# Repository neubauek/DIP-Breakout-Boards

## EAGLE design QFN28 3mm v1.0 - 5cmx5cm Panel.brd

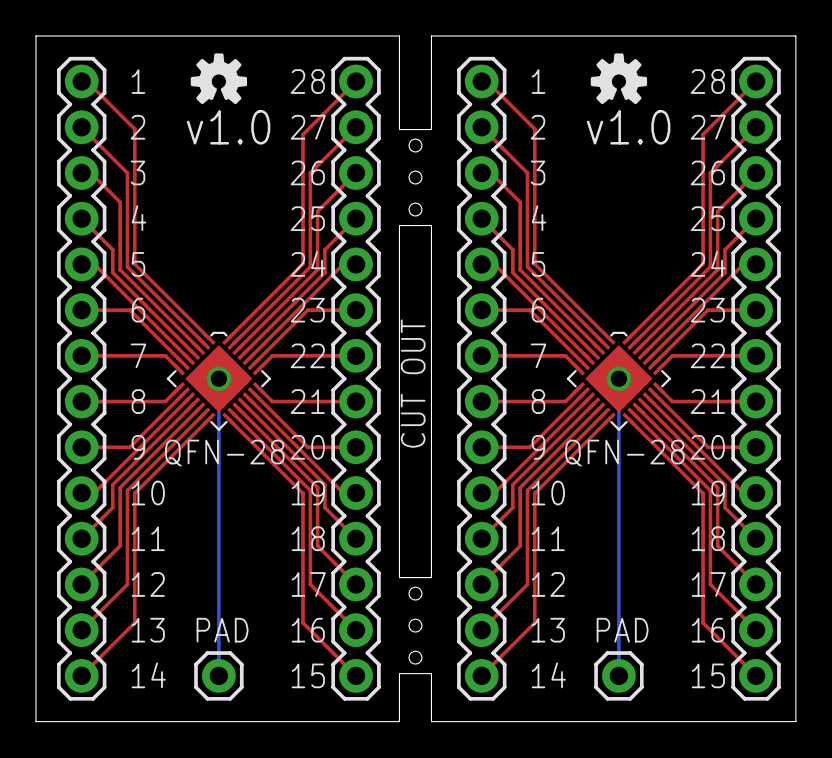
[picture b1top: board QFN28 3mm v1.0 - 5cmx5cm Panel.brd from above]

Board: 2 copper layers, 42.2 x 38.1 mm, 11 parts (0 on the bottom side), 58 nets.

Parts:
FRAME1: FRAME-LETTER; CREATIVE_COMMONS
JP1, JP2, JP3, JP4: M14; 1X14
PAD, PAD1: M01PTH; 1X01
U$1, U$3: QFN-28
U$2, U$4: OSHW-LOGO-S

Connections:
GND: PAD.1, U$1.29
GND1: PAD1.1, U$3.29
unnamed: JP1.14, U$1.1
unnamed: JP1.13, U$1.2
unnamed: JP1.12, U$1.3
unnamed: JP1.11, U$1.4
unnamed: JP1.10, U$1.5
unnamed: JP1.9, U$1.6
unnamed: JP1.8, U$1.7
unnamed: JP1.7, U$1.8
unnamed: JP1.6, U$1.9
unnamed: JP1.5, U$1.10
unnamed: JP1.4, U$1.11
unnamed: JP1.3, U$1.12
unnamed: JP1.2, U$1.13
unnamed: JP1.1, U$1.14
unnamed: JP2.1, U$1.15
unnamed: JP2.2, U$1.16
unnamed: JP2.3, U$1.17
unnamed: JP2.4, U$1.18
unnamed: JP2.5, U$1.19
unnamed: JP2.6, U$1.20
unnamed: JP2.7, U$1.21
unnamed: JP2.8, U$1.22
unnamed: JP2.9, U$1.23
unnamed: JP2.10, U$1.24
unnamed: JP2.11, U$1.25
unnamed: JP2.12, U$1.26
unnamed: JP2.13, U$1.27
unnamed: JP2.14, U$1.28
unnamed: JP3.14, U$3.1
unnamed: JP3.13, U$3.2
unnamed: JP3.12, U$3.3
unnamed: JP3.11, U$3.4
unnamed: JP3.10, U$3.5
unnamed: JP3.9, U$3.6
unnamed: JP3.8, U$3.7
unnamed: JP3.7, U$3.8
unnamed: JP3.6, U$3.9
unnamed: JP3.5, U$3.10
unnamed: JP3.4, U$3.11
unnamed: JP3.3, U$3.12
unnamed: JP3.2, U$3.13
unnamed: JP3.1, U$3.14
unnamed: JP4.1, U$3.15
unnamed: JP4.2, U$3.16
unnamed: JP4.3, U$3.17
unnamed: JP4.4, U$3.18
unnamed: JP4.5, U$3.19
unnamed: JP4.6, U$3.20
unnamed: JP4.7, U$3.21
unnamed: JP4.8, U$3.22
unnamed: JP4.9, U$3.23
unnamed: JP4.10, U$3.24
unnamed: JP4.11, U$3.25
unnamed: JP4.12, U$3.26
unnamed: JP4.13, U$3.27
unnamed: JP4.14, U$3.28

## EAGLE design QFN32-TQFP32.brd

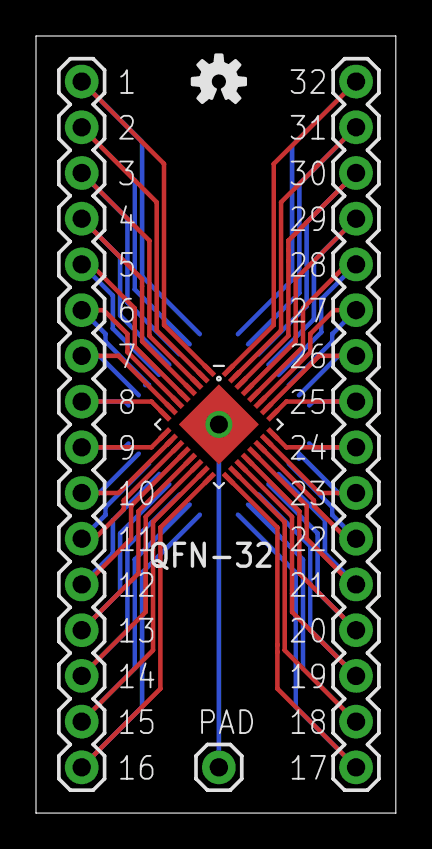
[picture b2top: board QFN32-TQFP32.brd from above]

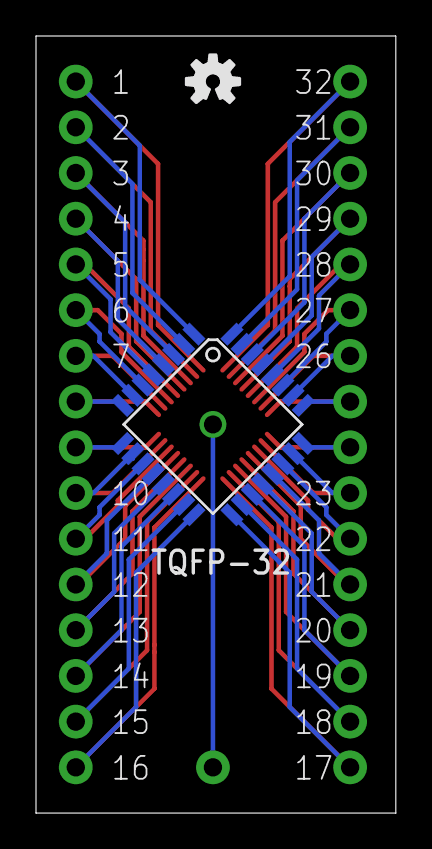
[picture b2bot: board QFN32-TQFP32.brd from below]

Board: 2 copper layers, 20.0 x 43.2 mm, 8 parts (2 on the bottom side), 33 nets.

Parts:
FRAME1: FRAME-LETTER; CREATIVE_COMMONS
JP1, JP2: M16PTH; 1X16
PAD: M01PTH; 1X01
QFN-32: QFN-32
TQFP-32: TQFP-3208MM; TQFP32-08
U$1, U$2: OSHW-LOGO-S

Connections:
GND: PAD.1, QFN-32.EP
unnamed: JP2.9, QFN-32.25, TQFP-32.8
unnamed: JP1.16, QFN-32.1, TQFP-32.32
unnamed: JP1.15, QFN-32.2, TQFP-32.31
unnamed: JP1.14, QFN-32.3, TQFP-32.30
unnamed: JP1.13, QFN-32.4, TQFP-32.29
unnamed: JP1.11, QFN-32.6, TQFP-32.27
unnamed: JP1.10, QFN-32.7, TQFP-32.26
unnamed: JP1.9, QFN-32.8, TQFP-32.25
unnamed: JP1.8, QFN-32.9, TQFP-32.24
unnamed: JP1.7, QFN-32.10, TQFP-32.23
unnamed: JP1.6, QFN-32.11, TQFP-32.22
unnamed: JP1.5, QFN-32.12, TQFP-32.21
unnamed: JP1.4, QFN-32.13, TQFP-32.20
unnamed: JP1.3, QFN-32.14, TQFP-32.19
unnamed: JP1.2, QFN-32.15, TQFP-32.18
unnamed: JP1.1, QFN-32.16, TQFP-32.17
unnamed: JP2.14, QFN-32.30, TQFP-32.3
unnamed: JP2.13, QFN-32.29, TQFP-32.4
unnamed: JP2.12, QFN-32.28, TQFP-32.5
unnamed: JP2.11, QFN-32.27, TQFP-32.6
unnamed: JP2.10, QFN-32.26, TQFP-32.7
unnamed: JP2.2, QFN-32.18, TQFP-32.15
unnamed: JP2.8, QFN-32.24, TQFP-32.9
unnamed: JP2.7, QFN-32.23, TQFP-32.10
unnamed: JP2.5, QFN-32.21, TQFP-32.12
unnamed: JP2.4, QFN-32.20, TQFP-32.13
unnamed: JP2.3, QFN-32.19, TQFP-32.14
unnamed: JP2.15, QFN-32.31, TQFP-32.2
unnamed: JP2.16, QFN-32.32, TQFP-32.1
unnamed: JP2.1, QFN-32.17, TQFP-32.16
unnamed: JP1.12, QFN-32.5, TQFP-32.28
unnamed: JP2.6, QFN-32.22, TQFP-32.11

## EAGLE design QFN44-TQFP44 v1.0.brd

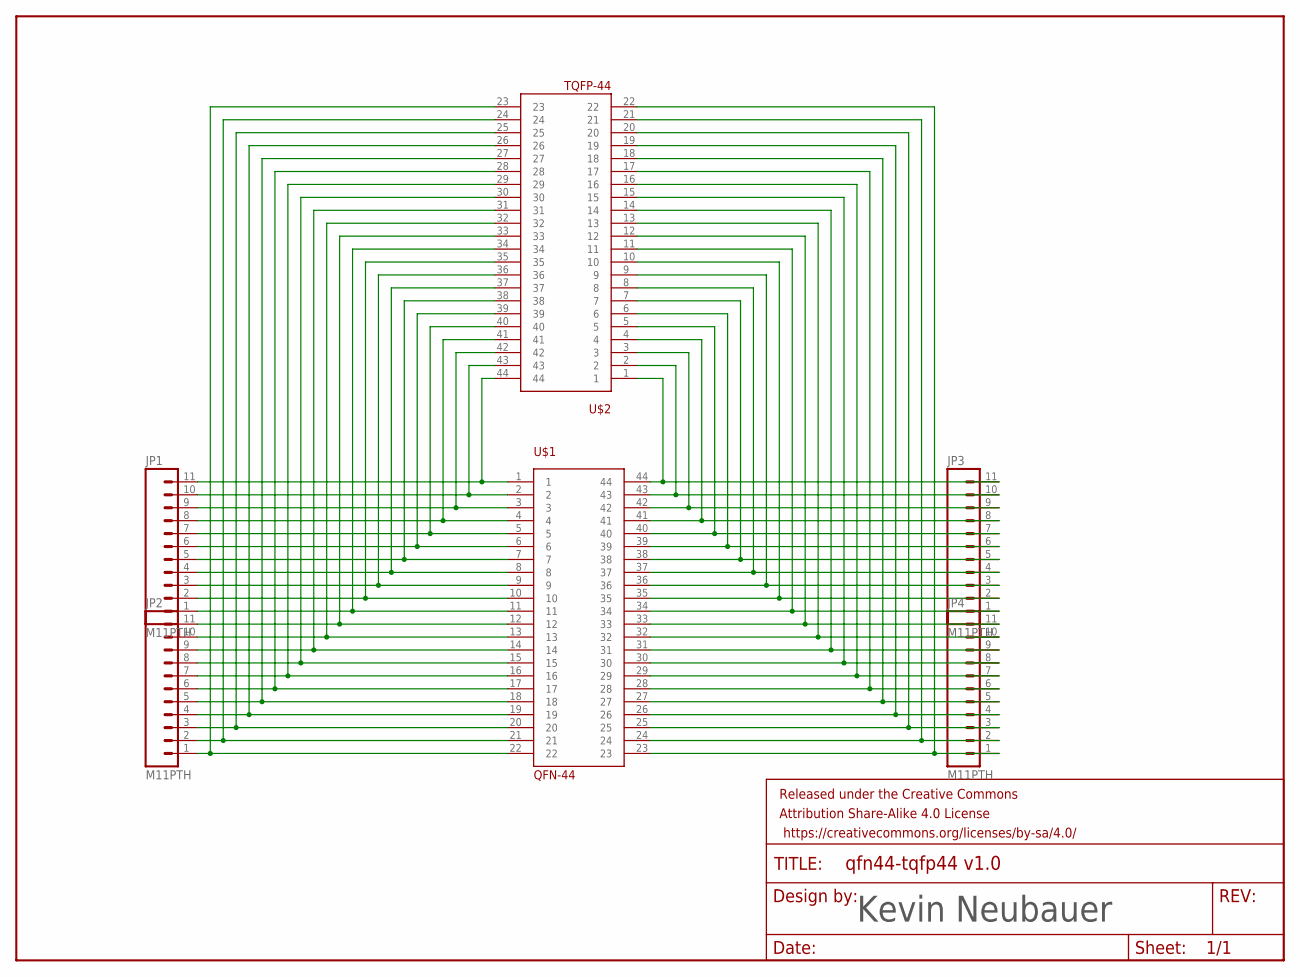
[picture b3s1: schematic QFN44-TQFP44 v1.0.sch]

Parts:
FRAME1: FRAME-LETTER; CREATIVE_COMMONS
JP1, JP2, JP3, JP4: M11PTH; 1X11
U$1: QFN-44
U$2: TQFP-44; TQFP44

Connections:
unnamed: JP1.11, U$1.1, U$2.44
unnamed: JP1.10, U$1.2, U$2.43
unnamed: JP1.9, U$1.3, U$2.42
unnamed: JP1.8, U$1.4, U$2.41
unnamed: JP1.7, U$1.5, U$2.40
unnamed: JP1.6, U$1.6, U$2.39
unnamed: JP1.5, U$1.7, U$2.38
unnamed: JP1.4, U$1.8, U$2.37
unnamed: JP1.3, U$1.9, U$2.36
unnamed: JP1.2, U$1.10, U$2.35
unnamed: JP1.1, U$1.11, U$2.34
unnamed: JP2.11, U$1.12, U$2.33
unnamed: JP2.10, U$1.13, U$2.32
unnamed: JP2.9, U$1.14, U$2.31
unnamed: JP2.8, U$1.15, U$2.30
unnamed: JP2.7, U$1.16, U$2.29
unnamed: JP2.6, U$1.17, U$2.28
unnamed: JP2.5, U$1.18, U$2.27
unnamed: JP2.4, U$1.19, U$2.26
unnamed: JP2.3, U$1.20, U$2.25
unnamed: JP2.2, U$1.21, U$2.24
unnamed: JP2.1, U$1.22, U$2.23
unnamed: JP3.11, U$1.44, U$2.1
unnamed: JP3.10, U$1.43, U$2.2
unnamed: JP3.7, U$1.40, U$2.5
unnamed: JP3.6, U$1.39, U$2.6
unnamed: JP3.5, U$1.38, U$2.7
unnamed: JP3.4, U$1.37, U$2.8
unnamed: JP3.3, U$1.36, U$2.9
unnamed: JP3.2, U$1.35, U$2.10
unnamed: JP3.1, U$1.34, U$2.11
unnamed: JP4.11, U$1.33, U$2.12
unnamed: JP4.10, U$1.32, U$2.13
unnamed: JP4.9, U$1.31, U$2.14
unnamed: JP4.8, U$1.30, U$2.15
unnamed: JP4.7, U$1.29, U$2.16
unnamed: JP4.6, U$1.28, U$2.17
unnamed: JP4.5, U$1.27, U$2.18
unnamed: JP4.4, U$1.26, U$2.19
unnamed: JP4.3, U$1.25, U$2.20
unnamed: JP4.2, U$1.24, U$2.21
unnamed: JP4.1, U$1.23, U$2.22
unnamed: JP3.9, U$1.42, U$2.3
unnamed: JP3.8, U$1.41, U$2.4

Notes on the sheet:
Kevin Neubauer

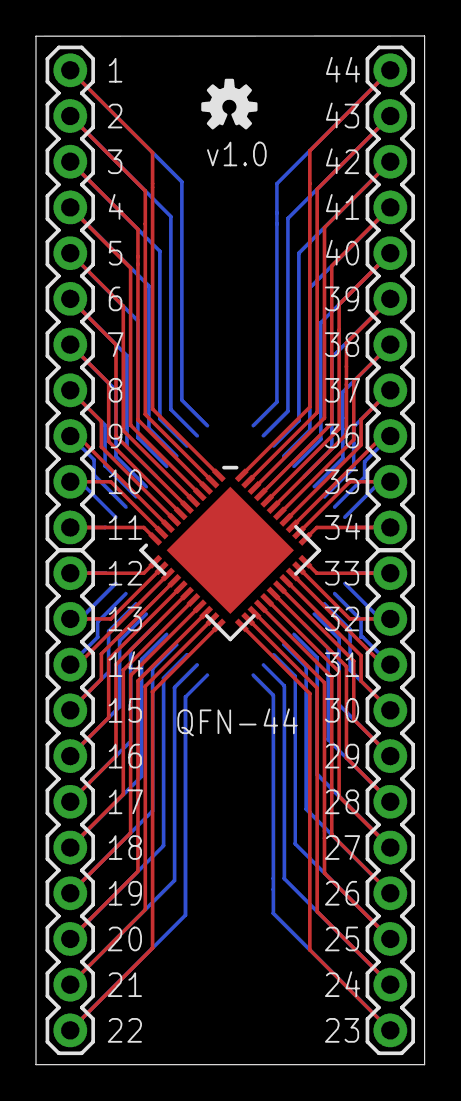
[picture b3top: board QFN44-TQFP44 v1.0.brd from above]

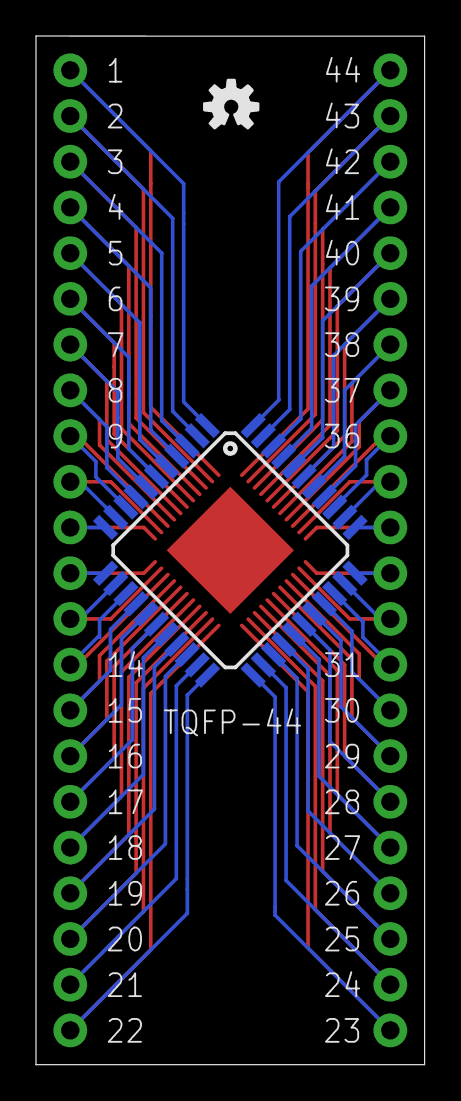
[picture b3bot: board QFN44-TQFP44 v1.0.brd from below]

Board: 2 copper layers, 21.6 x 57.1 mm, 9 parts (2 on the bottom side), 44 nets.

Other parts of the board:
U$3, U$4: OSHW-LOGO-S

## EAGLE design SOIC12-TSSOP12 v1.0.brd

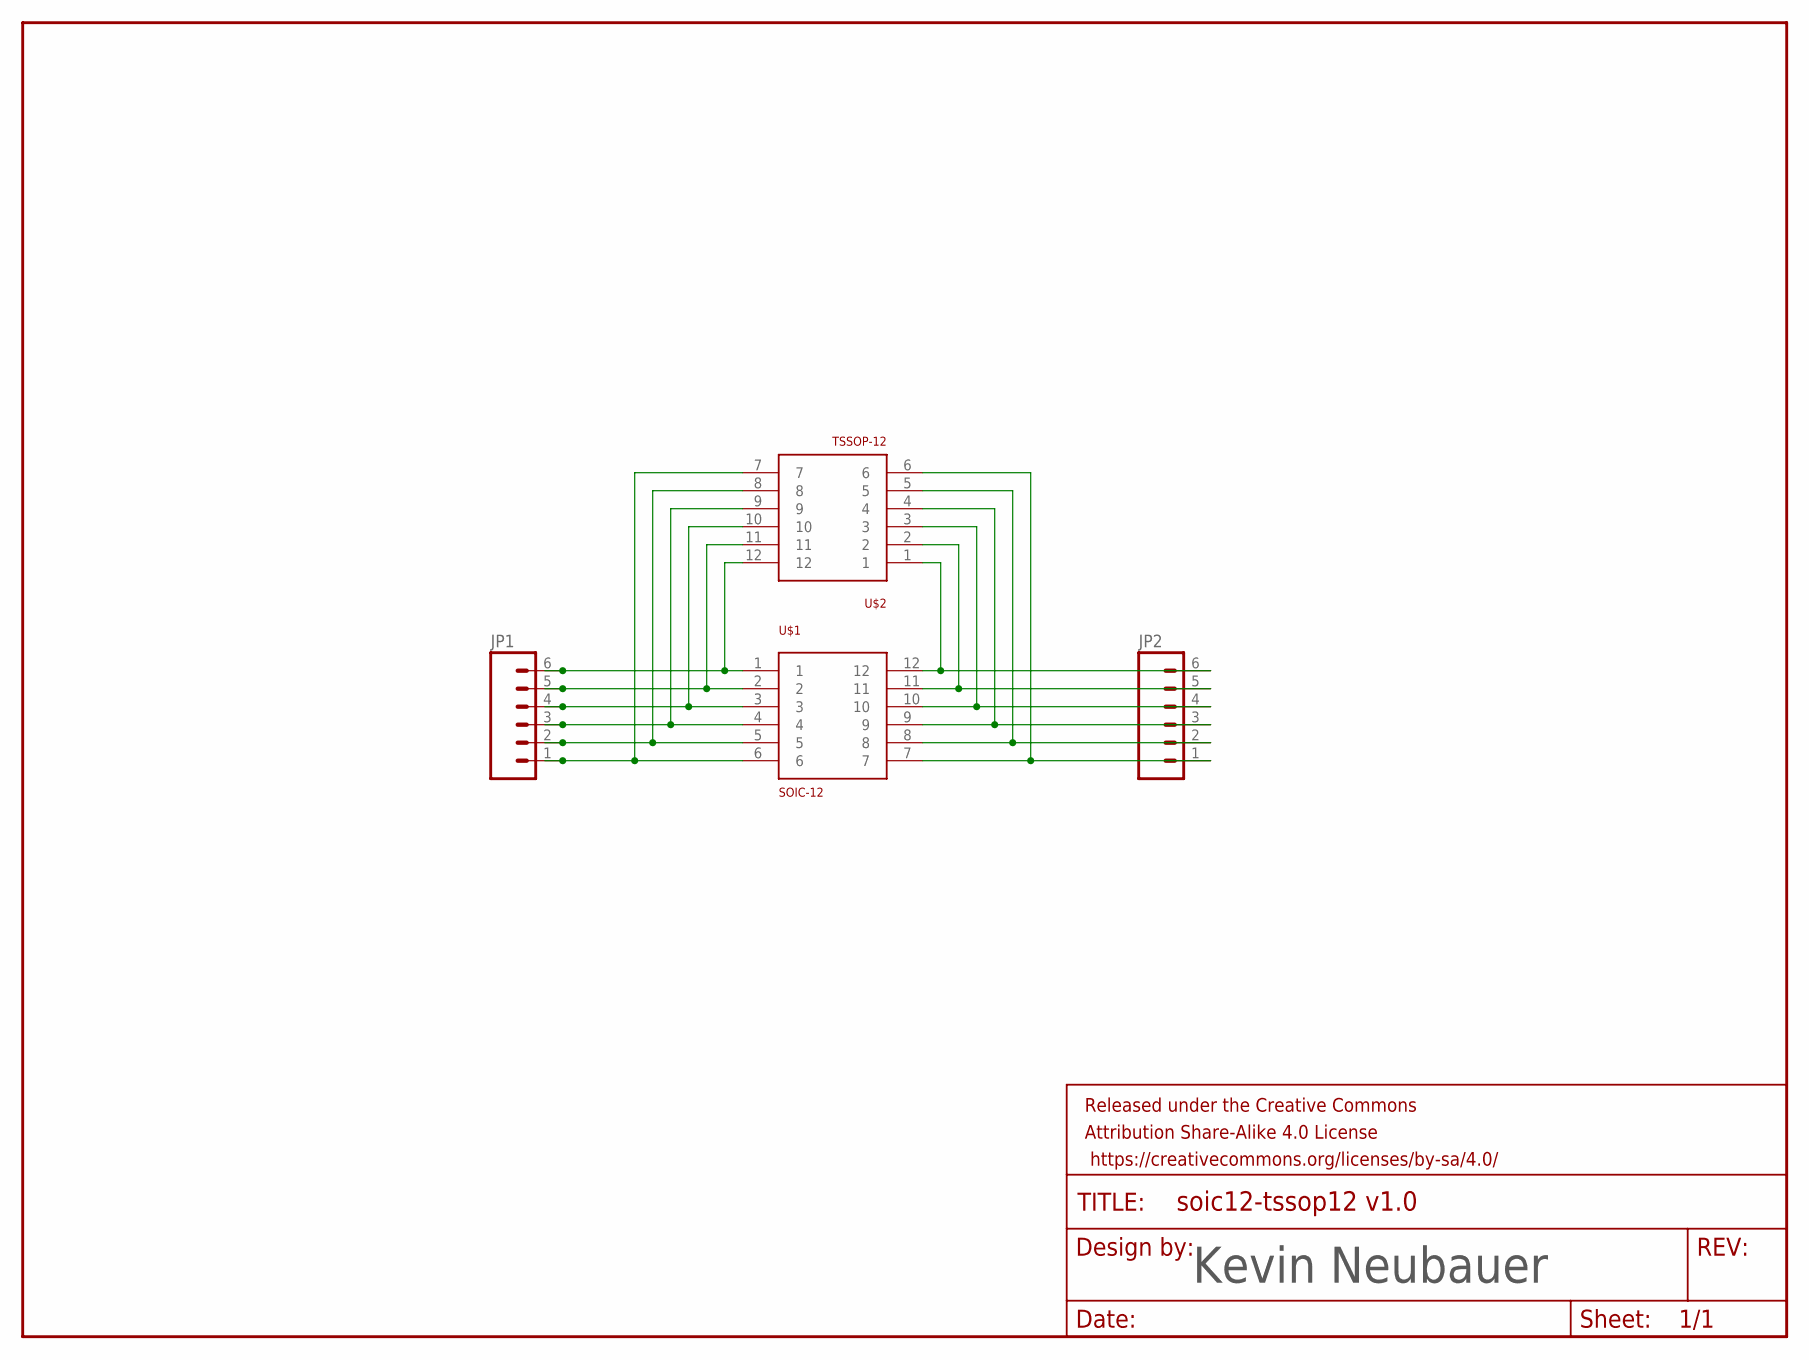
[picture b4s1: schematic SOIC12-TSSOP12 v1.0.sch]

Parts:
FRAME1: FRAME-LETTER; CREATIVE_COMMONS
JP1, JP2: M06NO_SILK; 1X06_NO_SILK
U$1: SOIC-12
U$2: TSSOP-12; TSSOP12

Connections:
unnamed: JP1.6, U$1.1, U$2.12
unnamed: JP1.5, U$1.2, U$2.11
unnamed: JP1.4, U$1.3, U$2.10
unnamed: JP1.3, U$1.4, U$2.9
unnamed: JP1.2, U$1.5, U$2.8
unnamed: JP1.1, U$1.6, U$2.7
unnamed: JP2.6, U$1.12, U$2.1
unnamed: JP2.5, U$1.11, U$2.2
unnamed: JP2.4, U$1.10, U$2.3
unnamed: JP2.3, U$1.9, U$2.4
unnamed: JP2.2, U$1.8, U$2.5
unnamed: JP2.1, U$1.7, U$2.6

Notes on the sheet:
Kevin Neubauer

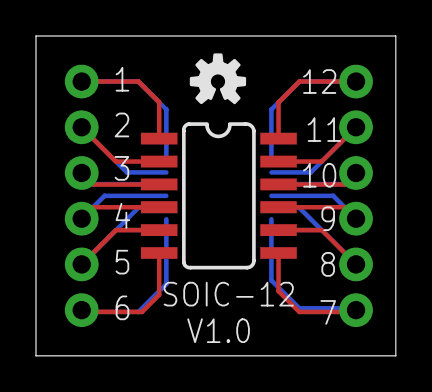
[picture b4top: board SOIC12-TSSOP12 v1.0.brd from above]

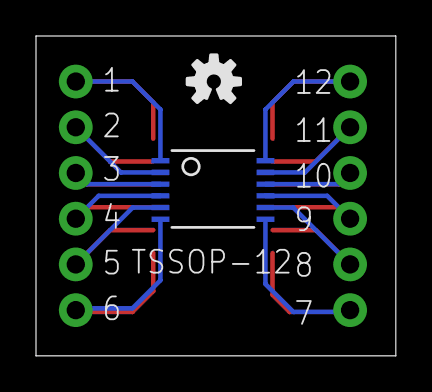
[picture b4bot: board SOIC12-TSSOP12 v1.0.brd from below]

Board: 2 copper layers, 20.0 x 17.8 mm, 7 parts (2 on the bottom side), 12 nets.

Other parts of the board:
U$3, U$4: OSHW-LOGO-S

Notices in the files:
parts and their libraries:
SparkFun-Connectors: Licensing: Creative Commons ShareAlike 4.0 International - https://creativecommons.org/licenses/by-sa/4.0
SparkFun-Aesthetics: Released under the Creative Commons Attribution Share-Alike 4.0 License
SparkFun-Aesthetics: https://creativecommons.org/licenses/by-sa/4.0
